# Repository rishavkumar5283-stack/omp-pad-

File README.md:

# omp-pad-
so its a macro pad made i made it in ki cad it has 12 key 
i have used these component 
1. one rasberry pi_pico
2. 12 cherrymx switch
3. droids (1N914)
4. rotatory encoder
5. female harder 04X01 for oled
   connection =

schematics=
thats it 
have a look at the pcb!!!!!!!!!!!!!!!!!!!!!!!!!!!!!!!!!!!!

KEY MAPING (FETUR OF EACH KEY)

Switch	Function	Shortcut

SW1 =	Copy	

SW2 =	Paste

SW3 =	Undo	

SW4 =	Screenshot tool	

SW5 =	Windows Search	

SW6 = Switch apps	

SW7 =	Save	

SW8 =	Select all

SW9 =	File Explorer	

SW10 = VS Code Command Palette

SW11 = Play/Pause media	

SW12 = Open Run dialog

i will upload the file as (code of omp pad) u can access it there 

Rotary encoder=Clockwise: Volume up,Anticlockwise: Volume down,Press: Unassigned

work of oled is to display tings i am displaying = (rishav / omp boy) 

References

KMK firmware: https://github.com/KMKfw/kmk_firmware

KMK display documentation: https://github.com/KMKfw/kmk_firmware/blob/main/docs/en/Display.md

KMK encoder documentation: https://github.com/KMKfw/kmk_firmware/blob/main/docs/en/encoder.md

CircuitPython: https://circuitpython.org/

Adafruit CircuitPython libraries: https://circuitpython.org/libraries/

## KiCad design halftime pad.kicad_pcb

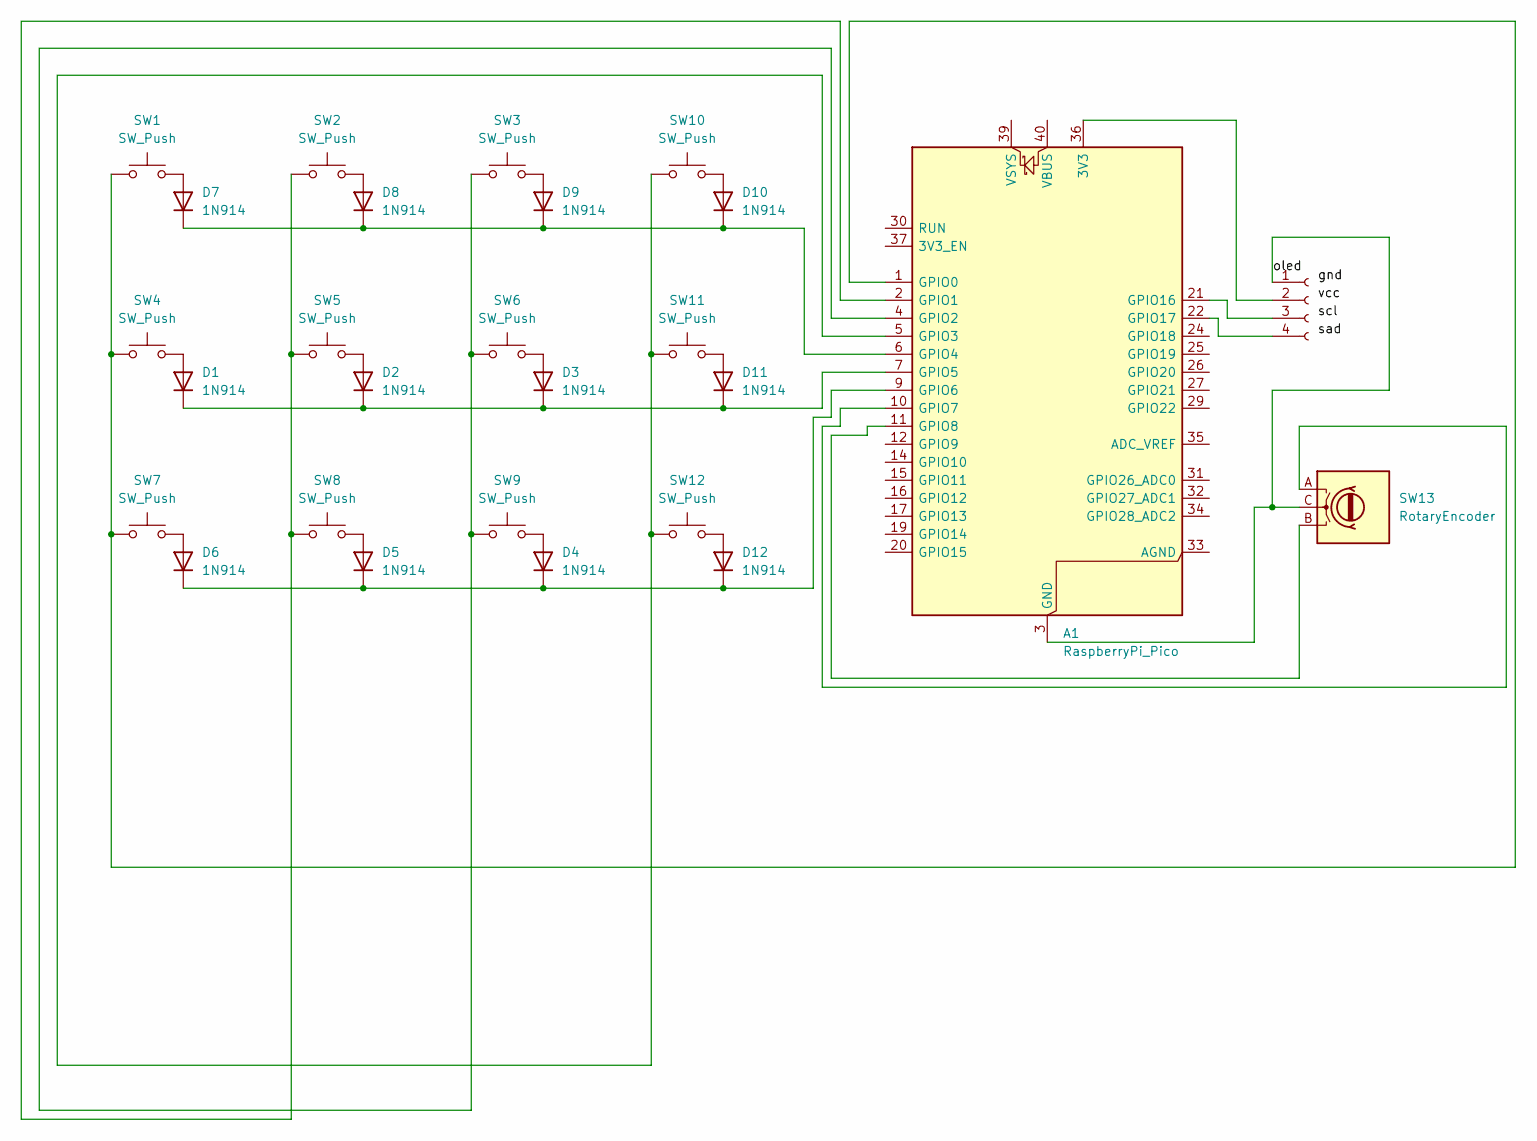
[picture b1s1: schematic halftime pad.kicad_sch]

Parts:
A1: RaspberryPi_Pico; RaspberryPi_Pico_Common_Unspecified
D1, D2, D3, D4, D5, D6, D7, D8, D9, D10, D11, D12: 1N914; D_DO-35_SOD27_P7.62mm_Horizontal
J1: Conn_01x04_Socket; NS-Tech_Grove_1x04_P2mm_Vertical
SW1, SW2, SW3, SW4, SW5, SW6, SW7, SW8, SW9, SW10, SW11, SW12: SW_Push; SW_Cherry_MX_1.00u_PCB
SW13: RotaryEncoder; RotaryEncoder_Bourns_Horizontal_PEC09-2xxxF-Nxxxx

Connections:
/oled: A1.3 (GND), A1.8 (GND), A1.13 (GND), A1.18 (GND), A1.23 (GND), A1.28 (GND), A1.38 (GND), J1.1, SW13.C
unnamed: A1.36 (3V3), J1.2
unnamed: A1.1 (GPIO0), SW1.1, SW4.1, SW7.1
unnamed: A1.2 (GPIO1), SW2.1, SW5.1, SW8.1
unnamed: A1.4 (GPIO2), SW3.1, SW6.1, SW9.1
unnamed: A1.5 (GPIO3), SW10.1, SW11.1, SW12.1
unnamed: A1.6 (GPIO4), D7.1 (K), D8.1 (K), D9.1 (K), D10.1 (K)
unnamed: A1.7 (GPIO5), D1.1 (K), D2.1 (K), D3.1 (K), D11.1 (K)
unnamed: A1.9 (GPIO6), D4.1 (K), D5.1 (K), D6.1 (K), D12.1 (K)
unnamed: A1.10 (GPIO7), SW13.A
unnamed: A1.11 (GPIO8), SW13.B
unnamed: A1.21 (GPIO16), J1.3
unnamed: A1.22 (GPIO17), J1.4
unnamed: D1.2 (A), SW4.2
unnamed: D2.2 (A), SW5.2
unnamed: D3.2 (A), SW6.2
unnamed: D4.2 (A), SW9.2
unnamed: D5.2 (A), SW8.2
unnamed: D6.2 (A), SW7.2
unnamed: D7.2 (A), SW1.2
unnamed: D8.2 (A), SW2.2
unnamed: D9.2 (A), SW3.2
unnamed: D10.2 (A), SW10.2
unnamed: D11.2 (A), SW11.2
unnamed: D12.2 (A), SW12.2

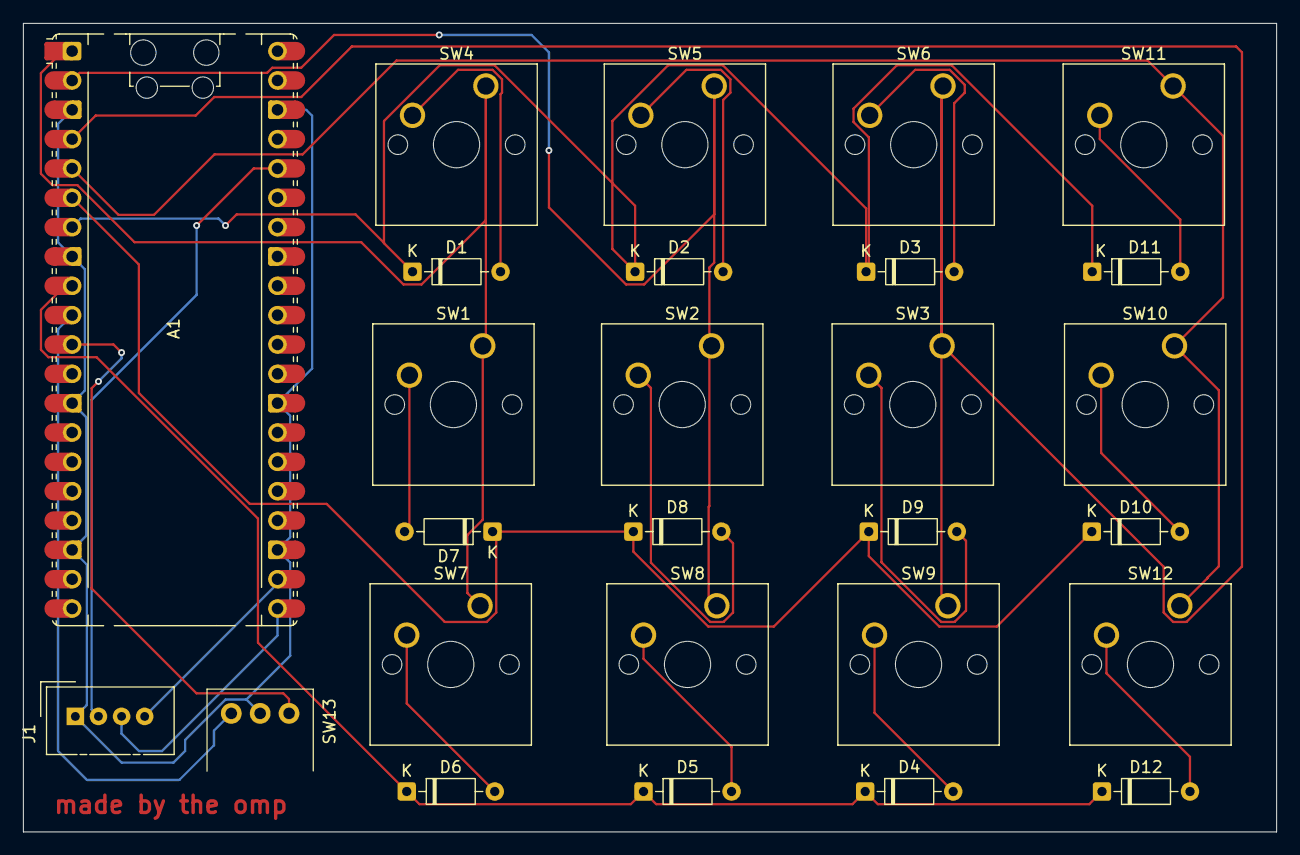
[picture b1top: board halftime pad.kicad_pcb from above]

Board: 2 copper layers, 108.5 x 70.0 mm, 27 parts (0 on the bottom side), 25 nets.

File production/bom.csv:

Designator,Footprint,Quantity,Value,LCSC Part #
A1,RaspberryPi_Pico_Common_Unspecified,1,RaspberryPi_Pico,
"D1, D10, D11, D12, D2, D3, D4, D5, D6, D7, D8, D9",D_DO-35_SOD27_P7.62mm_Horizontal,12,1N914,
J1,NS-Tech_Grove_1x04_P2mm_Vertical,1,Conn_01x04_Socket,
"SW1, SW10, SW11, SW12, SW2, SW3, SW4, SW5, SW6, SW7, SW8, SW9",SW_Cherry_MX_1.00u_PCB,12,SW_Push,
SW13,RotaryEncoder_Bourns_Horizontal_PEC09-2xxxF-Nxxxx,1,RotaryEncoder,
